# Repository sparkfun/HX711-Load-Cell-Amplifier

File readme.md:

HX711 Load Cell Amplifier
=======

*[SparkFun Load Cell Amplifier - HX711](https://www.sparkfun.com/products/13230)*

The SparkFun Load Cell Amplifier is a small breakout board for the HX711 IC that allows you to easily read load cells to measure weight. By connecting the amplifier to your microcontroller you will be able to read the changes in the resistance of the load cell and with some calibration you’ll be able to get very accurate weight measurements. This can be handy for creating your own industrial scale, process control, or simple presence detection of an object.

The HX711 uses a two wire interface (Clock and Data) for communication. Any microcontroller’s GPIO pins should work and numerous libraries have been written making it easy to read data from the HX711.

Load cells use a four wire wheatstone bridge to connect to the HX711. These are commonly colored RED, BLK, WHT, GRN, and YLW. Each color corresponds to the conventional color coding of load cells:

* Red (Excitation+ or VCC)
* Black (Excitation- or GND)
* White (Amplifier+, Signal+, or Output+)
* Green (A-, S-, or O-)
* Yellow (Shield)

The YLW pin acts as an optional input that is not hooked up to the strain gauge but is utilized to ground and shield against outside EMI (electromagnetic interference). Please keep in mind that some load cells might have slight variations in color coding.

Repository Contents
-------------------

* **/Production_Files** - Panelized version of the design for production
* **/datasheets** - Datasheet for HX711 IC
* **/firmware** - Example Arduino sketches
* **/hardware** - All Eagle design files (.brd, .sch)

Documentation
--------------
* **[Library](https://github.com/bogde/HX711)** - Arduino library for the HX711
* **[Getting Started with Load Cells](https://learn.sparkfun.com/tutorials/getting-started-with-load-cells)** - Introduction to Load Cells
* **[Hookup Guide](https://learn.sparkfun.com/tutorials/load-cell-amplifier-hx711-breakout-hookup-guide)** - Basic hookup guide for the Load Cell Amplifier

License Information
-------------------

This design is [OSHW](http://www.oshwa.org/definition/) and public domain but you buy me a beer if you use this and we meet someday ([Beerware license](http://en.wikipedia.org/wiki/Beerware)).

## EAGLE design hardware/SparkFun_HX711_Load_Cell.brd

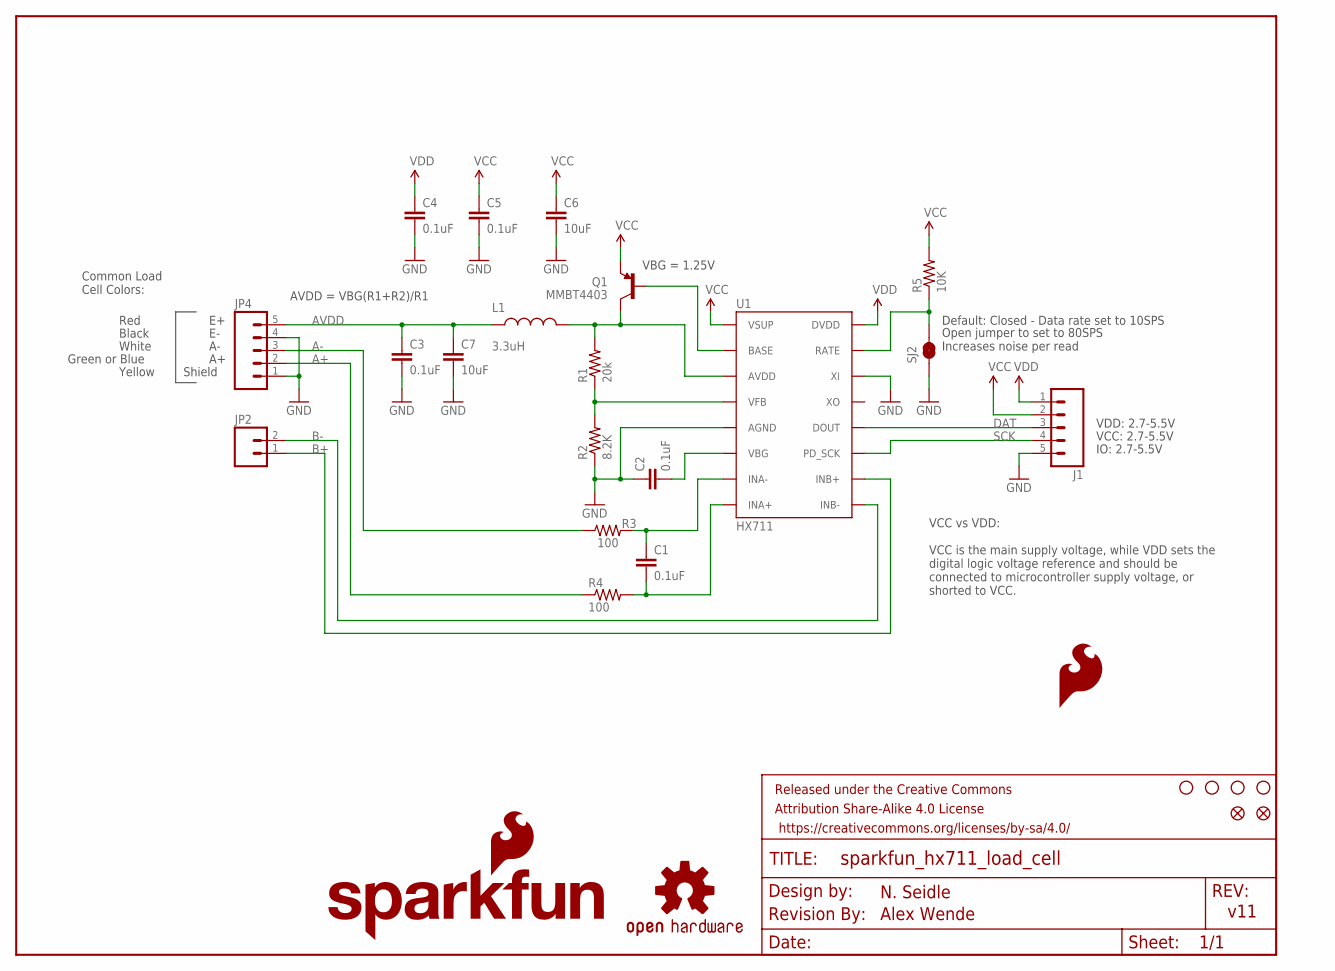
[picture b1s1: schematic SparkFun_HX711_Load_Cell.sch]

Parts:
C1, C2, C3, C4, C5: 0.1uF; 0603-CAP
C6, C7: 10uF; 1210
FID1, FID2: FIDUCIAL1X2; FIDUCIAL-1X2
FRAME1: FRAME-LETTER; CREATIVE_COMMONS
J1: M05PTH; 1X05
JP2: M02PTH; 1X02
JP4: M05PTH; 1X05
L1: 3.3uH; 0805
LOGO1: SFE_LOGO_NAME_FLAME.1_INCH; SFE_LOGO_NAME_FLAME_.1
LOGO3: SFE_LOGO_FLAME.1_INCH; SFE_LOGO_FLAME_.1
Q1: MMBT4403; SOT23-3
R1: 20k; 0603-RES
R2: 8.2K; 0603-RES
R3, R4: 100; 0603-RES
R5: 10K; 0603-RES
SJ2: JUMPER-PAD-2-NC_BY_TRACE; PAD-JUMPER-2-NC_BY_TRACE_YES_SILK
STANDOFF1, STANDOFF2, STANDOFF3, STANDOFF4: STAND-OFF
U1: HX711; SO16
U7: OSHW-LOGOS; OSHW-LOGO-S
U$1: REVISION

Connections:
A+: JP4.2, R4.1
A-: JP4.3, R3.1
AVDD: C3.1, C7.1, JP4.5, L1.1
B+: JP2.1, U1.10 (INB+)
B-: JP2.2, U1.9 (INB-)
DAT: J1.3, U1.12 (DOUT)
GND: C2.1, C3.2, C4.2, C5.2, C6.2, C7.2, J1.5, JP4.1, JP4.4, R2.1, SJ2.1, U1.5 (AGND), U1.14 (XI)
unnamed: R5.1, SJ2.2, U1.15 (RATE)
unnamed: C1.1, R3.2, U1.7 (INA-)
unnamed: C1.2, R4.2, U1.8 (INA+)
unnamed: Q1.1 (B), U1.2 (BASE)
unnamed: L1.2, Q1.3 (C), R1.2, U1.3 (AVDD)
unnamed: R1.1, R2.2, U1.4 (VFB)
unnamed: C2.2, U1.6 (VBG)
SCK: J1.4, U1.11 (PD_SCK)
VCC: C5.1, C6.1, J1.2, Q1.2 (E), R5.2, U1.1 (VSUP)
VDD: C4.1, J1.1, U1.16 (DVDD)

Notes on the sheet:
VCC: 2.7-5.5V
VBG = 1.25V
AVDD = VBG(R1+R2)/R1
Default: Closed - Data rate set to 10SPS
Open jumper to set to 80SPS Increases noise per read
Red
Black
White
Green or Blue
Common Load Cell Colors:
IO: 2.7-5.5V
Shield
Yellow
VDD: 2.7-5.5V
VCC vs VDD: VCC is the main supply voltage, while VDD sets the digital logic voltage reference and should be connected to microcontroller supply voltage, or shorted to VCC.
Alex Wende
N. Seidle
v11

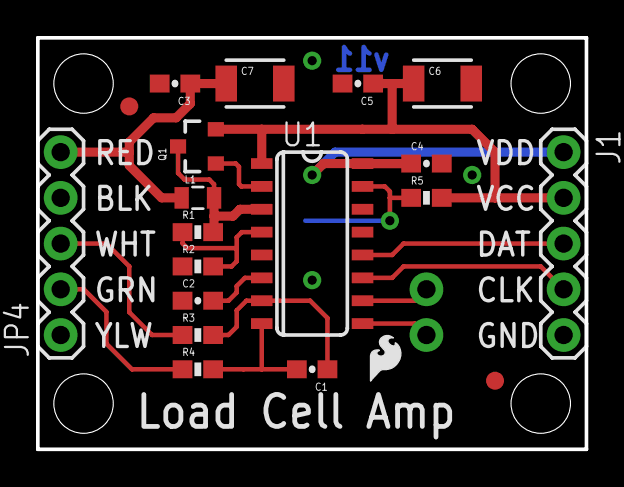
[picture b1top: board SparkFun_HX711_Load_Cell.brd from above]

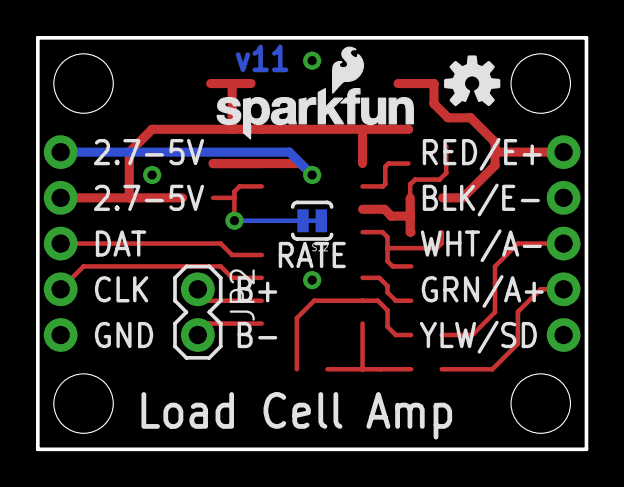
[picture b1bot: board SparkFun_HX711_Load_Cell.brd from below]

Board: 2 copper layers, 30.5 x 22.9 mm, 30 parts (4 on the bottom side), 17 nets.

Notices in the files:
parts and their libraries:
SparkFun-Connectors: Licensing: CC v3.0 Share-Alike You are welcome to use this library for commercial purposes.
SparkFun-Capacitors: Licensing: Creative Commons ShareAlike 4.0 International - https://creativecommons.org/licenses/by-sa/4.0
SparkFun-Aesthetics: Released under the Creative Commons
